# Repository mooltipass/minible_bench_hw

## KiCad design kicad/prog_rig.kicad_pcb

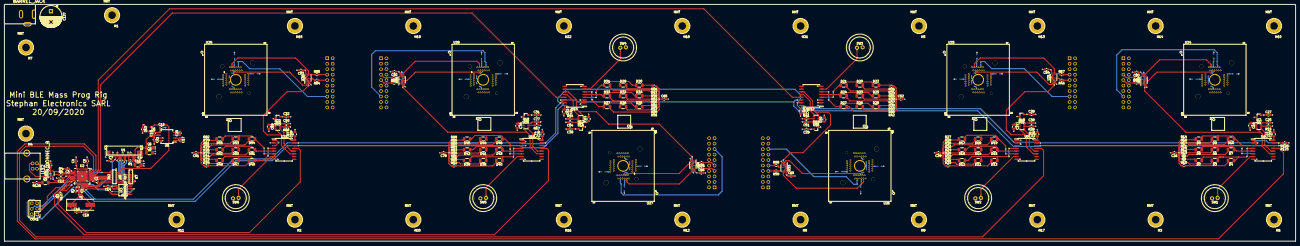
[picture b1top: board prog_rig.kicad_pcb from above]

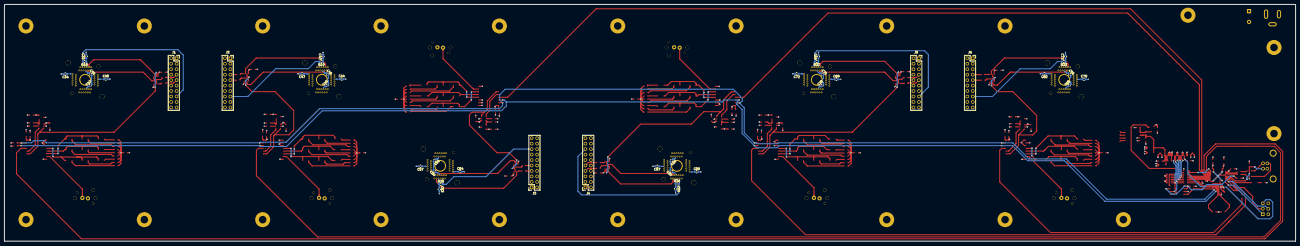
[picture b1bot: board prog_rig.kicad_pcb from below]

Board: 4 copper layers, 600.0 x 110.0 mm, 312 parts (42 on the bottom side), 205 nets.

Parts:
C1, C2, C3, C4, C7, C8, C9, C10, C14, C15, C19, C22, C26, C33, C34, C35, C39, C40, C42, C43, C44, C45, C47, C48, C52, C53, C54, C55, C57, C58, C59, C60, C61, C65, C67, C68, C69, C70, C72, C73, C74, C78, C79, C80, C82, C83, C84, C85, C86, C87, C91, C92, C93: 100nF; C_0603_1608Metric
C5, C6: 22uF; C_1206_3216Metric
C11: 4.7uF; C_1206_3216Metric
C12, C25, C27, C28, C29, C30, C31, C32, C38, C41, C46, C51, C56, C64, C66, C71, C77, C81, C90: 1uF; C_0603_1608Metric
C13, C21: 4.7uF; C_0603_1608Metric
C16, C18: 18pF; C_0603_1608Metric
C17, C20: 220nF; C_0603_1608Metric
C23, C24, C36, C37, C49, C50, C62, C63, C75, C76, C88, C89: 10uF; C_0805_2012Metric
C137: CP; CP_Radial_D10.0mm_P5.00mm
CON1: AVR-ISP-6; PinHeader_2x03_P2.54mm_Vertical
CON11: BARREL_JACK; BARREL-PJ-002AH
D1, D2, D3, D4, D5, D6, D7, D8, D9, D10, D11, D12, D13, D14, D15, D16, D17, D18, D19, D20, D21, D22, D23, D24, D25, D26, D27, D28, D29, D30, D31, D32, D33, D34, D35, D36, D37, D38, D39, D40, D41, D42, D43, D44, D45, D46, D47, D48, D49, D50, D51, D52, D53, D54, D55: LED; R_1206_3216Metric
H1, H2, H3, H4, H5, H6, H7, H8, H9, H10, H11, H12, H13, H14, H15, H16, H17, H18, H19, H20, H21, H22: MNT; HOLE_FIX_M3
J1, J2, J3, J4, J5, J6: Conn_ARM_JTAG_SWD_20; PinSocket_2x10_P2.54mm_Vertical
Q1: MOS_P; SOT-23
R1: 910k; R_0603_1608Metric
R2, R3, R18, R19, R20, R31, R32, R33, R127: 10k; R_0603_1608Metric
R4, R5: 22; R_0603_1608Metric
R6: 2k2; RNETWORK8_0603
R7: 4k7; RNETWORK8_0603
R8, R9, R10, R11, R12, R13, R14, R16, R17, R21, R22, R23, R24, R25, R26, R27, R29, R30, R34, R35, R36, R37, R38, R39, R40, R42, R43, R47, R48, R49, R50, R51, R52, R53, R55, R56, R60, R61, R62, R63, R64, R65, R66, R68, R69, R73, R74, R75, R76, R77, R78, R79, R81, R82: 1k; R_0603_1608Metric
R15, R28, R41, R54, R67, R80: 210k; R_0603_1608Metric
R44, R45, R46, R57, R58, R59, R70, R71, R72, R83, R84, R85: 50; R_0603_1608Metric
R125, R126: 2k2; R_0603_1608Metric
R128: 100; R_0603_1608Metric
SW1, SW2, SW3, SW4, SW5, SW6: SW_PUSH; SWITCH_K12P
U1: CON_UGM128032A6B01; CON_SFV24R-2STE1HLF
U2: ATMEGA32U4_QFN; QFN-44-1EP_7x7mm_P0.5mm_EP5.2x5.2mm
U3: AT45DB011D; SO8EN
U4: IP4234CZ6,125; TSOP-6_1.65x3.05mm_P0.95mm
U5: ST662ACD; SO-8_5.3x6.2mm_P1.27mm
U6, U9, U12, U15, U18, U21: PCA9554; SOIC-16W_7.5x10.3mm_P1.27mm
U7, U10, U13, U16, U19, U22: AP2553A; SOT-23-6
U8, U11, U14, U17, U20, U23: AP7333-33SAG-7; SOT-23
U24, U25, U26, U27, U28, U29: SAMD21G18A-MU; QFN-48(56)BT-0.5-01
U30, U31, U33, U34, U35, U36: SN74LVC2G66DCTR; SSOP-8_2.95x2.8mm_P0.65mm
U32: USB_CONNEC_B; USB-AU-Y1007-R
Y1: 16MHz; Crystal_SMD_HC49-SD

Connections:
+3V3: C7.2, C12.1, C14.1, U1.5, U2.6, U3.3, U3.5, U3.6
+5V: C1.1, C2.1, C3.1, C4.1, C8.1, C13.1, C22.1, C23.1, C24.1, C26.1, C35.1, C36.1, C37.1, C39.1, C48.1, C49.1, C50.1, C52.1, C61.1, C62.1, C63.1, C65.1, C74.1, C75.1, C76.1, C78.1, C83.1, C84.1, C85.1, C86.1, C87.1, C88.1, C89.1, C91.1, C92.1, C93.1, C137.1, CON1.2, CON11.1, Q1.2, R2.1, R6.8, R8.1, R9.1, R10.1, R11.1, R12.1, R13.1, R14.1, R16.1, R17.1, R21.1, R22.1, R23.1, R24.1, R25.1, R26.1, R27.1, R29.1, R30.1, R34.1, R35.1, R36.1, R37.1, R38.1, R39.1, R40.1, R42.1, R43.1, R47.1, R48.1, R49.1, R50.1, R51.1, R52.1, R53.1, R55.1, R56.1, R60.1, R61.1, R62.1, R63.1, R64.1, R65.1, R66.1, R68.1, R69.1, R73.1, R74.1, R75.1, R76.1, R77.1, R78.1, R79.1, R81.1, R82.1, R125.1, R126.1, U2.2, U2.14, U2.24, U2.34, U2.44, U6.16, U7.1, U9.1, U9.16, U10.1, U12.2, U12.16, U13.1, U15.1, U15.2, U15.16, U16.1, U18.3, U18.16, U19.1, U21.1, U21.3, U21.16, U22.1, U30.8, U31.8, U33.8, U34.8, U35.8, U36.8
+12V: C5.1, C6.1, C9.1, C19.1, C21.1, U1.23, U5.6
/BL_POWER: Q1.1, R6.7
/FLASH_HV_nS: R6.11, U2.28
/FLASH_nS: R6.6, R7.11, U3.4
/I2C_SCL: R125.2, U2.18, U6.14, U9.14, U12.14, U15.14, U18.14, U21.14
/I2C_SDA: R126.2, U2.19, U6.15, U9.15, U12.15, U15.15, U18.15, U21.15
/INT0: U2.31, U6.13
/INT1: U2.32, U9.13
/INT2: U2.30, U12.13
/INT3: U2.29, U15.13
/INT4: R3.2, U18.13
/INT5: R127.2, U21.13
/LCD_DnC: R6.3, R7.14, U1.10
/LCD_HV_DnC: R6.14, U2.25
/LCD_HV_SS: R6.12, U2.27
/LCD_HV_nRES: R6.13, U2.26
/LCD_SS: R6.5, R7.12, U1.8
/LCD_nRES: R6.4, R7.13, U1.9
/MISO: CON1.1, R127.1, U2.11
/MOSI: CON1.4, R3.1, U2.10
/Programming Socket #0/3V3_SOCKET: C27.1, C33.1, C34.1, C40.1, C42.1, R18.1, U8.2, U24.6, U24.17, U24.36, U24.44
/Programming Socket #0/LED1: D2.1, D3.1, D4.1, U6.4
/Programming Socket #0/LED2: D5.1, D6.1, D7.1, U6.5
/Programming Socket #0/LED3: D8.1, D9.1, D10.1, U6.6
/Programming Socket #0/PSU_EN: U6.11, U7.3, U30.3, U30.7
/Programming Socket #0/PSU_FAULT: U6.12, U7.4
/Programming Socket #0/SWCLK: U24.45, U30.2
/Programming Socket #0/SWDIO: U24.46, U30.6
/Programming Socket #0/SWITCH: SW1.1, U6.7
/Programming Socket #0/nRESET: J1.15, R18.2, U24.40
/Programming Socket #1/3V3_SOCKET: C28.1, C43.1, C44.1, C45.1, C47.1, R19.1, U11.2, U25.6, U25.17, U25.36, U25.44
/Programming Socket #1/LED1: D11.1, D12.1, D13.1, U9.4
/Programming Socket #1/LED2: D14.1, D15.1, D16.1, U9.5
/Programming Socket #1/LED3: D17.1, D18.1, D19.1, U9.6
/Programming Socket #1/PSU_EN: U9.11, U10.3, U31.3, U31.7
/Programming Socket #1/PSU_FAULT: U9.12, U10.4
/Programming Socket #1/SWCLK: U25.45, U31.2
/Programming Socket #1/SWDIO: U25.46, U31.6
/Programming Socket #1/SWITCH: SW2.1, U9.7
/Programming Socket #1/nRESET: J2.15, R19.2, U25.40
/Programming Socket #2/3V3_SOCKET: C29.1, C53.1, C54.1, C55.1, C57.1, R20.1, U14.2, U26.6, U26.17, U26.36, U26.44
/Programming Socket #2/LED1: D20.1, D21.1, D22.1, U12.4
/Programming Socket #2/LED2: D23.1, D24.1, D25.1, U12.5
/Programming Socket #2/LED3: D26.1, D27.1, D28.1, U12.6
/Programming Socket #2/PSU_EN: U12.11, U13.3, U33.3, U33.7
/Programming Socket #2/PSU_FAULT: U12.12, U13.4
/Programming Socket #2/SWCLK: U26.45, U33.2
/Programming Socket #2/SWDIO: U26.46, U33.6
/Programming Socket #2/SWITCH: SW3.1, U12.7
/Programming Socket #2/nRESET: J3.15, R20.2, U26.40
/Programming Socket #3/3V3_SOCKET: C30.1, C58.1, C59.1, C60.1, C67.1, R31.1, U17.2, U27.6, U27.17, U27.36, U27.44
/Programming Socket #3/LED1: D29.1, D30.1, D31.1, U15.4
/Programming Socket #3/LED2: D32.1, D33.1, D34.1, U15.5
/Programming Socket #3/LED3: D35.1, D36.1, D37.1, U15.6
/Programming Socket #3/PSU_EN: U15.11, U16.3, U34.3, U34.7
/Programming Socket #3/PSU_FAULT: U15.12, U16.4
/Programming Socket #3/SWCLK: U27.45, U34.2
/Programming Socket #3/SWDIO: U27.46, U34.6
/Programming Socket #3/SWITCH: SW4.1, U15.7
/Programming Socket #3/nRESET: J4.15, R31.2, U27.40
/Programming Socket #4/3V3_SOCKET: C31.1, C68.1, C69.1, C70.1, C72.1, R32.1, U20.2, U28.6, U28.17, U28.36, U28.44
/Programming Socket #4/LED1: D38.1, D39.1, D40.1, U18.4
/Programming Socket #4/LED2: D41.1, D42.1, D43.1, U18.5
/Programming Socket #4/LED3: D44.1, D45.1, D46.1, U18.6
/Programming Socket #4/PSU_EN: U18.11, U19.3, U35.3, U35.7
/Programming Socket #4/PSU_FAULT: U18.12, U19.4
/Programming Socket #4/SWCLK: U28.45, U35.2
/Programming Socket #4/SWDIO: U28.46, U35.6
/Programming Socket #4/SWITCH: SW5.1, U18.7
/Programming Socket #4/nRESET: J5.15, R32.2, U28.40
/Programming Socket #5/3V3_SOCKET: C32.1, C73.1, C79.1, C80.1, C82.1, R33.1, U23.2, U29.6, U29.17, U29.36, U29.44
/Programming Socket #5/LED1: D47.1, D48.1, D49.1, U21.4
/Programming Socket #5/LED2: D50.1, D51.1, D52.1, U21.5
/Programming Socket #5/LED3: D53.1, D54.1, D55.1, U21.6
/Programming Socket #5/PSU_EN: U21.11, U22.3, U36.3, U36.7
/Programming Socket #5/PSU_FAULT: U21.12, U22.4
/Programming Socket #5/SWCLK: U29.45, U36.2
/Programming Socket #5/SWDIO: U29.46, U36.6
/Programming Socket #5/SWITCH: SW6.1, U21.7
/Programming Socket #5/nRESET: J6.15, R33.2, U29.40
/RESET: CON1.5, R2.2, U2.13
/SCK: CON1.3, U2.9
/SPI2_CLK: R6.2, R7.15, U1.13, U3.2
/SPI2_HV_MOSI: R6.16, U2.21
/SPI2_HV_SCK: R6.15, U2.22
/SPI2_MISO: U2.20, U3.8
/SPI2_MOSI: R6.1, R7.16, U1.14, U3.1
/USB_D+: R5.2, U2.4
/USB_D-: R4.2, U2.3
/USB_VBUS: C10.1, U2.7, U4.5, U32.1
GND: C1.2, C2.2, C3.2, C4.2, C5.2, C6.2, C7.1, C8.2, C9.2, C10.2, C11.2, C12.2, C13.2, C14.2, C15.2, C16.2, C18.2, C21.2, C22.2, C23.2, C24.2, C25.2, C26.2, C27.2, C28.2, C29.2, C30.2, C31.2, C32.2, C33.2, C34.2, C35.2, C36.2, C37.2, C38.2, C39.2, C40.2, C41.2, C42.2, C43.2, C44.2, C45.2, C46.2, C47.2, C48.2, C49.2, C50.2, C51.2, C52.2, C53.2, C54.2, C55.2, C56.2, C57.2, C58.2, C59.2, C60.2, C61.2, C62.2, C63.2, C64.2, C65.2, C66.2, C67.2, C68.2, C69.2, C70.2, C71.2, C72.2, C73.2, C74.2, C75.2, C76.2, C77.2, C78.2, C79.2, C80.2, C81.2, C82.2, C83.2, C84.2, C85.2, C86.2, C87.2, C88.2, C89.2, C90.2, C91.2, C92.2, C93.2, C137.2, CON1.6, CON11.2, CON11.3, J1.4, J1.6, J1.8, J1.10, J1.12, J1.14, J1.16, J1.18, J1.20, J2.4, J2.6, J2.8, J2.10, J2.12, J2.14, J2.16, J2.18, J2.20, J3.4, J3.6, J3.8, J3.10, J3.12, J3.14, J3.16, J3.18, J3.20, J4.4, J4.6, J4.8, J4.10, J4.12, J4.14, J4.16, J4.18, J4.20, J5.4, J5.6, J5.8, J5.10, J5.12, J5.14, J5.16, J5.18, J5.20, J6.4, J6.6, J6.8, J6.10, J6.12, J6.14, J6.16, J6.18, J6.20, R1.2, R7.1, R7.2, R7.3, R7.4, R7.5, R7.6, R15.1, R28.1, R41.1, R54.1, R67.1, R80.1, R128.2, SW1.2, SW2.2, SW3.2, SW4.2, SW5.2, SW6.2, U1.2, U1.3, U1.6, U1.7, U1.11, U1.12, U1.16, U1.17, U1.18, U1.19, U1.20, U1.25, U1.26, U2.5, U2.15, U2.23, U2.35, U2.43, U2.45, U3.7, U4.2, U5.7, U5.8, U6.1, U6.2, U6.3, U6.8, U7.2, U8.3, U9.2, U9.3, U9.8, U10.2, U11.3, U12.1, U12.3, U12.8, U13.2, U14.3, U15.3, U15.8, U16.2, U17.3, U18.1, U18.2, U18.8, U19.2, U20.3, U21.2, U21.8, U22.2, U23.3, U24.5, U24.18, U24.35, U24.42, U24.49, U25.5, U25.18, U25.35, U25.42, U25.49, U26.5, U26.18, U26.35, U26.42, U26.49, U27.5, U27.18, U27.35, U27.42, U27.49, U28.5, U28.18, U28.35, U28.42, U28.49, U29.5, U29.18, U29.35, U29.42, U29.49, U30.4, U31.4, U32.4, U32.5, U32.6, U33.4, U34.4, U35.4, U36.4
unnamed: C11.1, U1.22
unnamed: C15.1, C19.2, Q1.3, U5.5
unnamed: C16.1, U2.16, Y1.1
unnamed: C17.1, U5.2
unnamed: C17.2, U5.1
unnamed: C18.1, U2.17, Y1.2
unnamed: C20.1, U5.3
unnamed: C20.2, U5.4
unnamed: C25.1, U7.6, U8.1
unnamed: C38.1, U10.6, U11.1
unnamed: C41.1, U24.43
unnamed: C46.1, U25.43
unnamed: C51.1, U13.6, U14.1
unnamed: C56.1, U26.43
unnamed: C64.1, U16.6, U17.1
unnamed: C66.1, U27.43
unnamed: C71.1, U28.43
unnamed: C77.1, U19.6, U20.1
unnamed: C81.1, U29.43
unnamed: C90.1, U22.6, U23.1
unnamed: D1.1, R128.1
unnamed: D1.2, U2.8
unnamed: D2.2, R8.2
unnamed: D3.2, R9.2
unnamed: D4.2, R10.2
unnamed: D5.2, R11.2
unnamed: D6.2, R12.2
unnamed: D7.2, R13.2
unnamed: D8.2, R14.2
unnamed: D9.2, R16.2
unnamed: D10.2, R17.2
unnamed: D11.2, R21.2
unnamed: D12.2, R22.2
unnamed: D13.2, R23.2
unnamed: D14.2, R24.2
unnamed: D15.2, R25.2
unnamed: D16.2, R26.2
unnamed: D17.2, R27.2
unnamed: D18.2, R29.2
unnamed: D19.2, R30.2
unnamed: D20.2, R34.2
unnamed: D21.2, R35.2
unnamed: D22.2, R36.2
unnamed: D23.2, R37.2
unnamed: D24.2, R38.2
unnamed: D25.2, R39.2
unnamed: D26.2, R40.2
unnamed: D27.2, R42.2
unnamed: D28.2, R43.2
unnamed: D29.2, R47.2
unnamed: D30.2, R48.2
unnamed: D31.2, R49.2
unnamed: D32.2, R50.2
unnamed: D33.2, R51.2
unnamed: D34.2, R52.2
unnamed: D35.2, R53.2
unnamed: D36.2, R55.2
unnamed: D37.2, R56.2
unnamed: D38.2, R60.2
unnamed: D39.2, R61.2
unnamed: D40.2, R62.2
unnamed: D41.2, R63.2
unnamed: D42.2, R64.2
unnamed: D43.2, R65.2
unnamed: D44.2, R66.2
unnamed: D45.2, R68.2
unnamed: D46.2, R69.2
unnamed: D47.2, R73.2
unnamed: D48.2, R74.2
unnamed: D49.2, R75.2
unnamed: D50.2, R76.2
unnamed: D51.2, R77.2
unnamed: D52.2, R78.2
unnamed: D53.2, R79.2
unnamed: D54.2, R81.2
unnamed: D55.2, R82.2
unnamed: J1.7, R45.2
unnamed: J1.9, R44.1
unnamed: J2.7, R57.2
unnamed: J2.9, R46.1
unnamed: J3.7, R59.2
unnamed: J3.9, R58.1
unnamed: J4.7, R71.2
unnamed: J4.9, R70.1
unnamed: J5.7, R83.2
unnamed: J5.9, R72.1
unnamed: J6.7, R85.2
unnamed: J6.9, R84.1
unnamed: R1.1, U1.21
unnamed: R4.1, U4.4
unnamed: R5.1, U4.3
unnamed: R6.9, R6.10, U2.33
unnamed: R15.2, U7.5
unnamed: R28.2, U10.5
unnamed: R41.2, U13.5
unnamed: R44.2, U30.1
unnamed: R45.1, U30.5
unnamed: R46.2, U31.1
unnamed: R54.2, U16.5
unnamed: R57.1, U31.5
unnamed: R58.2, U33.1
unnamed: R59.1, U33.5
unnamed: R67.2, U19.5
unnamed: R70.2, U34.1
unnamed: R71.1, U34.5
unnamed: R72.2, U35.1
unnamed: R80.2, U22.5
unnamed: R83.1, U35.5
unnamed: R84.2, U36.1
unnamed: R85.1, U36.5
unnamed: U4.6, U32.2
unnamed: U4.1, U32.3

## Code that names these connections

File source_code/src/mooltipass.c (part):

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    /* init gpio extenders */
    for (uint8_t id = 0; id < 6; id++)
    {
        /* pin mapping: 0 LED1, 1 LED2, 2 LED3, 3 switch, 6 psu_en, 7 psu_fault */
        writeDataToI2C(0x70 | (id << 1), 3, 0x88);
        /* reset outputs in case it is a quick reboot */
        writeDataToI2C(0x70 | (id << 1), 1, 0x07);
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
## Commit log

2021-01-10 cleaning up
2021-01-10 gitignore update

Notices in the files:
source_code/src/mooltipass.c:
Copyright [2014] [Mathieu Stephan]
